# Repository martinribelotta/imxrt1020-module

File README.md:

# imxrt1020-module
iMX RT 1020 CPU module

## Schematics

### Main

### Power system

### GPIO and interfaces

### Memory and storage

### Power schemas

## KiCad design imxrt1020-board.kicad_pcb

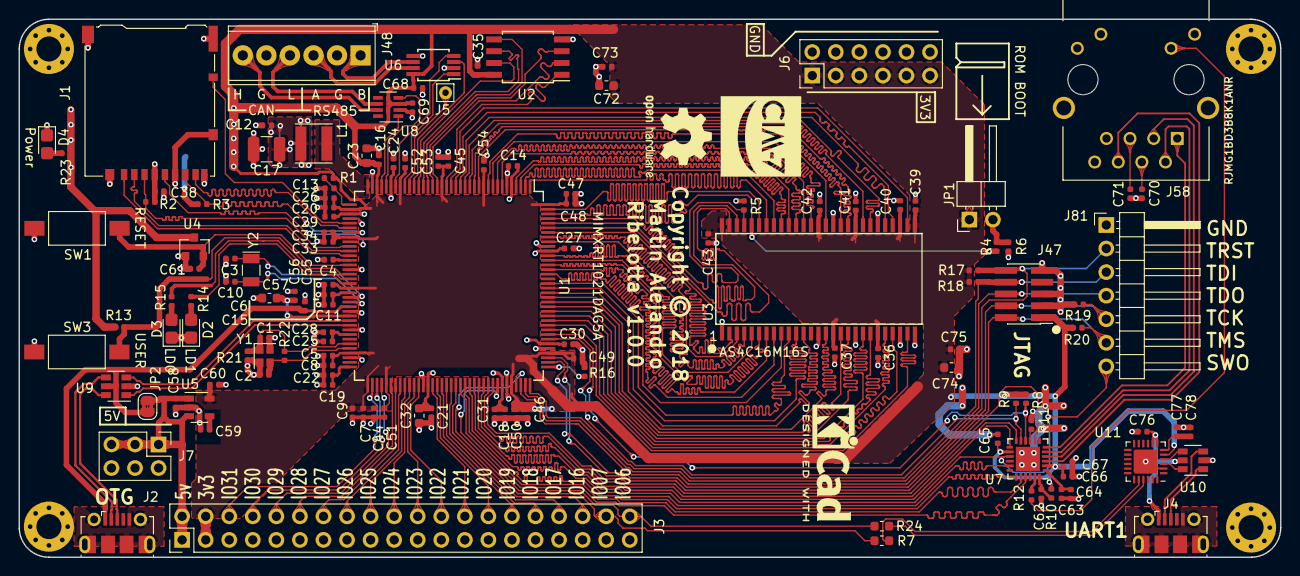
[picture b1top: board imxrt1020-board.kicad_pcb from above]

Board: 2 copper layers, 136.0 x 58.0 mm, 141 parts (0 on the bottom side), 143 nets.

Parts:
C1, C2: 4.7p; C_0402_1005Metric
C3, C10: 18p; C_0402_1005Metric
C4, C6, C8, C9, C11, C12, C13, C14, C16, C18, C19, C20, C21, C24, C27, C28, C29, C30: 0.22u; C_0402_1005Metric
C5, C15, C22, C25, C26, C31, C33, C44, C45, C46, C47, C64, C67, C73, C75, C77: 4.7u; C_0402_1005Metric
C7, C55, C58, C60, C61, C76: 1u; C_0402_1005Metric
C17: 33u; C_1210_3225Metric
C23, C32: 22u; C_0603_1608Metric
C34, C35, C36, C37, C38, C39, C40, C41, C42, C43, C48, C49, C50, C51, C52, C53, C54, C56, C62, C65, C66, C68, C69, C70, C71, C78: 0.1u; C_0402_1005Metric
C57, C72, C74: 10u; C_0603_1608Metric
C59, C63: 2.2u; C_0402_1005Metric
D2, D3, D4: RED; LED_0805_2012Metric_Castellated
J1: Micro_SD_Card_Det; microSD_HC_Hirose_DM3AT-SF-PEJM5
J2, J4: USB_OTG; USB_Micro-B_Molex-105017-0001
J3: Conn_02x20_Odd_Even; Pin_Header_Straight_2x20_Pitch2.54mm
J5: IO3_24; Pin_D0.7mm_L6.5mm_W1.8mm_FlatFork
J6: PWR1; PinHeader_2x06_P2.54mm_Vertical
J7: PWR2; PinHeader_2x03_P2.54mm_Vertical
J47: JTAG; PinHeader_2x05_P1.27mm_Vertical_SMD
J48: Conn_01x06; TerminalBlock_Phoenix_MPT-0,5-6-2.54_1x06_P2.54mm_Horizontal
J58: RJMG1BD3B8K1ANR; CONN_RJMG1BD3B8K1ANR
J81: Conn_01x07; PinHeader_1x07_P2.54mm_Horizontal
JP1: ROMBOOT; PinHeader_1x02_P2.54mm_Horizontal
JP2: USB_SHORT; SolderJumper-2_P1.3mm_Bridged2Bar_RoundedPad1.0x1.5mm
L1: 4.7u; L_Taiyo-Yuden_MD-4040
LOGO1: Logo_Open_Hardware_Small; OSHW-Logo2_9.8x8mm_SilkScreen
LOGO2: Logo_Open_Hardware_Small; KiCad-Logo2_6mm_SilkScreen
LOGO3: Logo_Open_Hardware_Small; ciaa_7-logo
MH1, MH2, MH3, MH4: HOLE; MountingHole_2.7mm_M2.5_Pad_Via
R1: 30K; R_0402_1005Metric
R2, R3, R4, R5, R8, R9, R10, R13, R16, R17, R18, R19, R20: 10K; R_0402_1005Metric
R6: 1K; R_0402_1005Metric
R7, R24: 0R; R_0603_1608Metric
R11: 6.49K %1; R_0402_1005Metric
R12, R14, R15, R23: 220R; R_0402_1005Metric
R21: 2.2M; R_0402_1005Metric
R22: 1M; R_0402_1005Metric
SW1: RST; SW_SPST_FSMSM
SW3: WAKE; SW_SPST_FSMSM
U1: imx_rt1020-qfp144; LQFP-144_20x20mm_Pitch0.5mm
U2: IS25LP064A-JBLE; SOIJ-8_5.3x5.3mm_Pitch1.27mm
U3: AS4C16M16S; TSOP_II_54
U4: TPS3839DBZ; SOT-23
U5: MIC5219-3.3; SOT-23-5
U6: ISL3178E; MSOP-8_3x3mm_Pitch0.65mm
U7: KSZ8081RNA; QFN-24-1EP_4x4mm_Pitch0.5mm
U8: TCAN332D; SOT-23-8
U9, U10: USBLC6-2; SOT-23-6
U11: CP2102N-A01-GQFN24; QFN-24-1EP_4x4mm_P0.5mm_EP2.6x2.6mm
Y1: 24MHz; Crystal_SMD_2016-4Pin_2.0x1.6mm
Y2: 32.768Khz; Crystal_SMD_MicroCrystal_CC7V-T1A-2Pin_3.2x1.5mm

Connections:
+3V3: C5.1, C6.1, C7.1, C8.1, C9.1, C16.1, C20.1, C23.1, C26.1, C33.1, C34.1, C35.1, C36.1, C37.1, C38.1, C39.1, C40.1, C41.1, C42.1, C43.1, C44.1, C45.1, C46.1, C47.1, C48.1, C49.1, C50.1, C51.1, C52.1, C53.1, C54.1, C60.1, C65.1, C66.1, C67.1, C68.1, C69.1, C72.1, C73.1, C74.1, C75.1, J1.4, J3.3, J3.4, J6.1, J6.3, J6.5, J6.7, J6.9, J6.11, J47.1, JP1.1, R1.1, R2.1, R3.1, R8.1, R9.1, R10.1, R13.2, R17.1, R18.1, R20.1, R23.1, U1.11, U1.20, U1.29, U1.34, U1.38, U1.44, U1.55, U1.69, U1.73, U1.77, U1.104, U1.112, U1.144, U2.8, U3.1, U3.3, U3.9, U3.14, U3.27, U3.43, U3.49, U4.3, U5.5, U6.8, U7.2, U7.14, U8.3, U11.5
+5V: C55.1, C58.1, J2.1, J3.1, J3.2, J7.1, J7.3, J7.5, JP2.1, JP2.2, U1.59, U5.1, U5.3, U9.5
/Debug UART/BDBGD+: U10.6, U11.3
/Debug UART/BDBGD-: U10.4, U11.4
/Debug UART/DBGD+: J4.3, U10.1
/Debug UART/DBGD-: J4.2, U10.3
/Debug UART/DBG_VBUS: C76.2, J4.1, U10.5, U11.7, U11.8
/GPIO/A_OTG_D+: U1.63, U9.1
/GPIO/A_OTG_D-: U1.62, U9.3
/GPIO/CAN_H: J48.6, U8.7
/GPIO/CAN_L: J48.4, U8.6
/GPIO/DBG_UART_RX: J3.40, R24.1, U1.101
/GPIO/DBG_UART_TX: J3.38, R7.1, U1.105
/GPIO/ENET_CRS_DV: J81.7, U1.97, U7.15
/GPIO/ENET_LED: J58.L3, R12.2
/GPIO/ENET_MDC: R9.2, U1.115, U7.11
/GPIO/ENET_MDIO: R8.2, U1.116, U7.10
/GPIO/ENET_RX+: J58.R3, U7.4
/GPIO/ENET_RX-: J58.R6, U7.3
/GPIO/ENET_RXD0: U1.98, U7.13
/GPIO/ENET_RXD1: U1.99, U7.12
/GPIO/ENET_RX_ER: U1.96, U7.17
/GPIO/ENET_TX+: J58.R1, U7.6
/GPIO/ENET_TX-: J58.R2, U7.5
/GPIO/ENET_TXD0: U1.94, U7.20
/GPIO/ENET_TXD1: U1.93, U7.21
/GPIO/ENET_TX_CLK: U1.100, U7.8
/GPIO/ENET_TX_EN: U1.95, U7.19
/GPIO/GPIO1_16: J3.36, U1.92
/GPIO/GPIO1_17: J3.34, U1.91
/GPIO/GPIO1_18: J3.32, U1.90
/GPIO/GPIO1_19: J3.30, U1.89
/GPIO/GPIO1_20: J3.28, U1.88
/GPIO/GPIO1_21: J3.26, U1.87
/GPIO/GPIO1_22: J3.24, U1.84
/GPIO/GPIO1_23: J3.22, U1.83
/GPIO/GPIO1_24: J3.20, U1.82
/GPIO/GPIO1_25: J3.18, U1.81
/GPIO/GPIO1_26: J3.16, U1.80
/GPIO/GPIO1_27: J3.14, U1.79
/GPIO/GPIO1_28: J3.12, U1.78
/GPIO/GPIO1_29: J3.10, U1.76
/GPIO/GPIO1_30: J3.8, U1.75
/GPIO/GPIO1_31: J3.6, U1.74
/GPIO/JTAG_TCK: J47.4, J81.5, R19.2, U1.110
/GPIO/JTAG_TDI: J47.8, J81.3, R18.2, U1.108
/GPIO/JTAG_TDO: J47.6, J81.4, U1.107
/GPIO/JTAG_TMS: J47.2, J81.6, R20.2, U1.111
/GPIO/JTAG_TRST: J47.10, J81.2, R17.2, U1.106
/GPIO/OTG_D+: J2.3, U9.6
/GPIO/OTG_D-: J2.2, U9.4
/GPIO/RS485_A: J48.1, U6.6
/GPIO/RS485_B: J48.3, U6.7
/GPIO/RS485_RX: U1.28, U6.1
/GPIO/RS485_TX: U1.30, U6.4
/MEMORY/CAN_RX: U1.32, U8.4
/MEMORY/CAN_TX: U1.33, U8.1
/MEMORY/GPIO3_24: J5.1, U1.27
/MEMORY/GPIO3_25: U1.26, U6.3
/MEMORY/QSPI_CLK: U1.24, U2.6
/MEMORY/QSPI_CS: U1.19, U2.1
/MEMORY/QSPI_Q0: U1.23, U2.5
/MEMORY/QSPI_Q1: U1.21, U2.2
/MEMORY/QSPI_Q2: U1.22, U2.3
/MEMORY/QSPI_Q3: U1.25, U2.7
/MEMORY/SDRAM_A0: R4.1, U1.142, U3.23
/MEMORY/SDRAM_A1: R5.1, U1.141, U3.24
/MEMORY/SDRAM_A2: U1.140, U3.25
/MEMORY/SDRAM_A3: U1.139, U3.26
/MEMORY/SDRAM_A4: U1.138, U3.29
/MEMORY/SDRAM_A5: U1.137, U3.30
/MEMORY/SDRAM_A6: U1.136, U3.31
/MEMORY/SDRAM_A7: U1.133, U3.32
/MEMORY/SDRAM_A8: U1.132, U3.33
/MEMORY/SDRAM_A9: U1.131, U3.34
/MEMORY/SDRAM_A10: U1.143, U3.22
/MEMORY/SDRAM_A11: U1.130, U3.35
/MEMORY/SDRAM_A12: U1.129, U3.36
/MEMORY/SDRAM_BA0: U1.2, U3.20
/MEMORY/SDRAM_BA1: U1.1, U3.21
/MEMORY/SDRAM_CAS: U1.7, U3.17
/MEMORY/SDRAM_CKE: U1.127, U3.37
/MEMORY/SDRAM_CLK: U1.126, U3.38
/MEMORY/SDRAM_CS: U1.3, U3.19
/MEMORY/SDRAM_LDQM: U1.9, U3.15
/MEMORY/SDRAM_Q0: U1.18, U3.2
/MEMORY/SDRAM_Q1: U1.17, U3.4
/MEMORY/SDRAM_Q2: U1.16, U3.5
/MEMORY/SDRAM_Q3: U1.15, U3.7
/MEMORY/SDRAM_Q4: U1.14, U3.8
/MEMORY/SDRAM_Q5: U1.13, U3.10
/MEMORY/SDRAM_Q6: U1.12, U3.11
/MEMORY/SDRAM_Q7: U1.10, U3.13
/MEMORY/SDRAM_Q8: U1.124, U3.42
/MEMORY/SDRAM_Q9: U1.123, U3.44
/MEMORY/SDRAM_Q10: U1.122, U3.45
/MEMORY/SDRAM_Q11: U1.121, U3.47
/MEMORY/SDRAM_Q12: U1.120, U3.48
/MEMORY/SDRAM_Q13: U1.119, U3.50
/MEMORY/SDRAM_Q14: U1.118, U3.51
/MEMORY/SDRAM_Q15: U1.117, U3.53
/MEMORY/SDRAM_RAS: U1.4, U3.18
/MEMORY/SDRAM_UDQM: U1.125, U3.39
/MEMORY/SDRAM_WE: U1.8, U3.16
/MEMORY/SD_CLK: J1.5, U1.45
/MEMORY/SD_CMD: J1.3, R2.2, U1.46
/MEMORY/SD_D0: J1.7, R3.2, U1.43
/MEMORY/SD_D1: J1.8, U1.42
/MEMORY/SD_D2: J1.1, U1.48
/MEMORY/SD_D3: J1.2, U1.47
/MEMORY/SD_SW: J1.10, U1.41
/POWER/DCDC_OUT: C12.1, C14.1, C17.1, C18.1, C21.1, C24.1, C27.1, C29.1, C30.1, C31.1, C32.1, L1.2, U1.5, U1.31, U1.39, U1.86, U1.102, U1.114, U1.134
GND: C1.2, C2.2, C3.2, C4.2, C5.2, C6.2, C7.2, C8.2, C9.2, C10.2, C11.2, C12.2, C13.2, C14.2, C15.2, C16.2, C17.2, C18.2, C19.2, C20.2, C21.2, C22.2, C23.2, C24.2, C25.2, C26.2, C27.2, C28.2, C29.2, C30.2, C31.2, C32.2, C33.2, C34.2, C35.2, C36.2, C37.2, C38.2, C39.2, C40.2, C41.2, C42.2, C43.2, C44.2, C45.2, C46.2, C47.2, C48.2, C49.2, C50.2, C51.2, C52.2, C53.2, C54.2, C55.2, C56.2, C57.2, C58.2, C59.2, C60.2, C61.2, C62.2, C63.2, C64.2, C65.2, C66.2, C67.2, C68.2, C69.2, C70.2, C71.2, C72.2, C73.2, C74.2, C75.2, C76.1, C77.1, C78.1, D2.1, D3.1, D4.1, J1.6, J1.9, J1.11, J2.5, J2.6, J3.5, J3.7, J3.9, J3.11, J3.13, J3.15, J3.17, J3.19, J3.21, J3.23, J3.25, J3.27, J3.29, J3.31, J3.33, J3.35, J3.37, J3.39, J4.5, J4.6, J6.2, J6.4, J6.6, J6.8, J6.10, J6.12, J7.2, J7.4, J7.6, J47.3, J47.5, J47.9, J48.2, J48.5, J58.1, J58.2, J58.L4, J58.R8, J81.1, MH1.1, MH2.1, MH3.1, MH4.1, R5.2, R6.2, R11.1, R16.2, R19.1, R21.1, SW1.2, SW3.2, U1.6, U1.35, U1.40, U1.51, U1.60, U1.64, U1.70, U1.85, U1.103, U1.113, U1.135, U2.4, U3.6, U3.12, U3.28, U3.41, U3.46, U3.52, U3.54, U4.1, U5.2, U6.2, U6.5, U7.22, U7.25, U8.2, U9.2, U10.2, U11.2, U11.25, Y1.2, Y1.4
unnamed: C1.1, R21.2, R22.1, U1.67, Y1.1
unnamed: C2.1, R22.2, U1.68, Y1.3
unnamed: C3.1, U1.57, Y2.1
unnamed: C4.1, U1.49
unnamed: C10.1, U1.58, Y2.2
unnamed: C11.1, C15.1, U1.56
unnamed: C13.1, R1.2, U1.37
unnamed: C19.1, C22.1, U1.72
unnamed: C25.1, C28.1, U1.65
unnamed: C56.1, C57.1, U1.61
unnamed: C59.1, U5.4
unnamed: C61.1, SW1.1, U1.50, U4.2
unnamed: C62.1, R10.2, U7.24
unnamed: C63.1, C64.1, U7.1
unnamed: C70.1, J58.R4
unnamed: C71.1, J58.R5
unnamed: C77.2, C78.2, U11.6
unnamed: D2.2, R14.2
unnamed: D3.2, R15.2
unnamed: D4.2, R23.2
unnamed: JP1.2, R4.2, R6.1
unnamed: L1.1, U1.36
unnamed: R7.2, U11.20
unnamed: R11.2, U7.9
unnamed: R12.1, U7.23
unnamed: R13.1, SW3.1, U1.52
unnamed: R14.1, U1.54
unnamed: R15.1, U1.53
unnamed: R16.1, U1.109
unnamed: R24.2, U11.21

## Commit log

2018-07-03 First verion (work in progress)
2018-07-03 Add board size measures
2018-07-03 Add 3dview image to readme
2018-07-03 Fix image path in readme
2018-07-03 Tune length of ethernet MAC to PHY lines
2018-07-03 Change 3v3@1A regulator by AZ1084-3.3@5A
2018-07-03 Fix gnd of regulator Signed-off-by: Martin Ribelotta <martinribelotta@gmail.com>
2018-07-03 Add GPIO legends (in progress)
2018-07-03 Add WAKE button and GPIO leds, enance GND connections
2018-07-03 Update README image
2018-07-03 More GND rework
2018-07-04 Circuit improves
    - Add power capacitors for PCB sectores (bottom rigth, top left)
    - Add mouting holes
    - Improve castelated and GND planes
    - Improve silkscreen legends
    - Improve puttons/leds possition
    - Improve USB-OTG lines shielding
2018-07-05 Add USB EMI filter, more silkscreen enances
2018-07-07 Minor changes on PCB
2018-07-07 Add schematic images to doc and enance README.md
2018-07-08 Change oscilators footprints and types matching ref design
2018-07-09 Enance USB EMI and filter circuit. Replace L1 (DC/DC) with correct part-number
2018-07-11 Change R/C to 0402 footprint
2018-07-18 Change USB protection, more silkscreen enances
2018-07-18 Add SDRAM 3d model
2018-08-08 Change 485/CAN connector to bornier. Relayout this area
2018-08-08 Change BOOT dip-witch for standard 0.1'' spacing (more cheap)
2018-08-08 Add 0.1'' pin header for jtag (non standard)
2018-08-10 Change boot dual switch by boot SPDT switch to BOOT0.
    BOOT1 is always pulldown
2018-08-11 Add SWD/CRS_DV into JTAG connector.
    Closes #4
    Rationate: The simulation in 50MHz of CRS/DV not show degradation of
    3rd armonic.
2018-08-11 Tune track length of ETH data lines
2018-08-11 Update images, README.md and PCB sylkscreen for reflect the changes
2018-08-11 First route of 6mil/6mil experiment
2018-08-12 Save commit after kicad-5 migration
2018-09-03 Finished major route on 6/6mils tech.
2018-09-03 Update some footprints and retune SDRAM for broken nets
2018-09-03 Update images
2018-09-04 Add logos
2018-09-08 Size rework
2018-09-08 Add untracked files for size rework
2018-09-08 Tune track length of RMII&microSD and move C59 to make space for GPIO silkscreens
2018-09-08 Add break-jumper inner USB VBUS and +5V I/O
2018-09-08 Update schematic images
2018-09-08 DRC pass!!!!
2018-09-08 Update schematics and images
2018-09-08 Some minor changes on silkscreen
2018-09-08 Modify corners to rounded
2018-09-08 Change pwr in caps footprint
2018-09-09 Add part ID and digikey ID, make bom, rework some parts of power and generate gerbers
2018-09-09 Update 3d image
2018-11-27 Plot and update images
2018-12-08 Add power schema image
2020-03-13 Update README.md
    Fixed a missing link to power-schemes.png.

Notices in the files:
imxrt1020-board.kicad_pcb:
Copyright © 2018
